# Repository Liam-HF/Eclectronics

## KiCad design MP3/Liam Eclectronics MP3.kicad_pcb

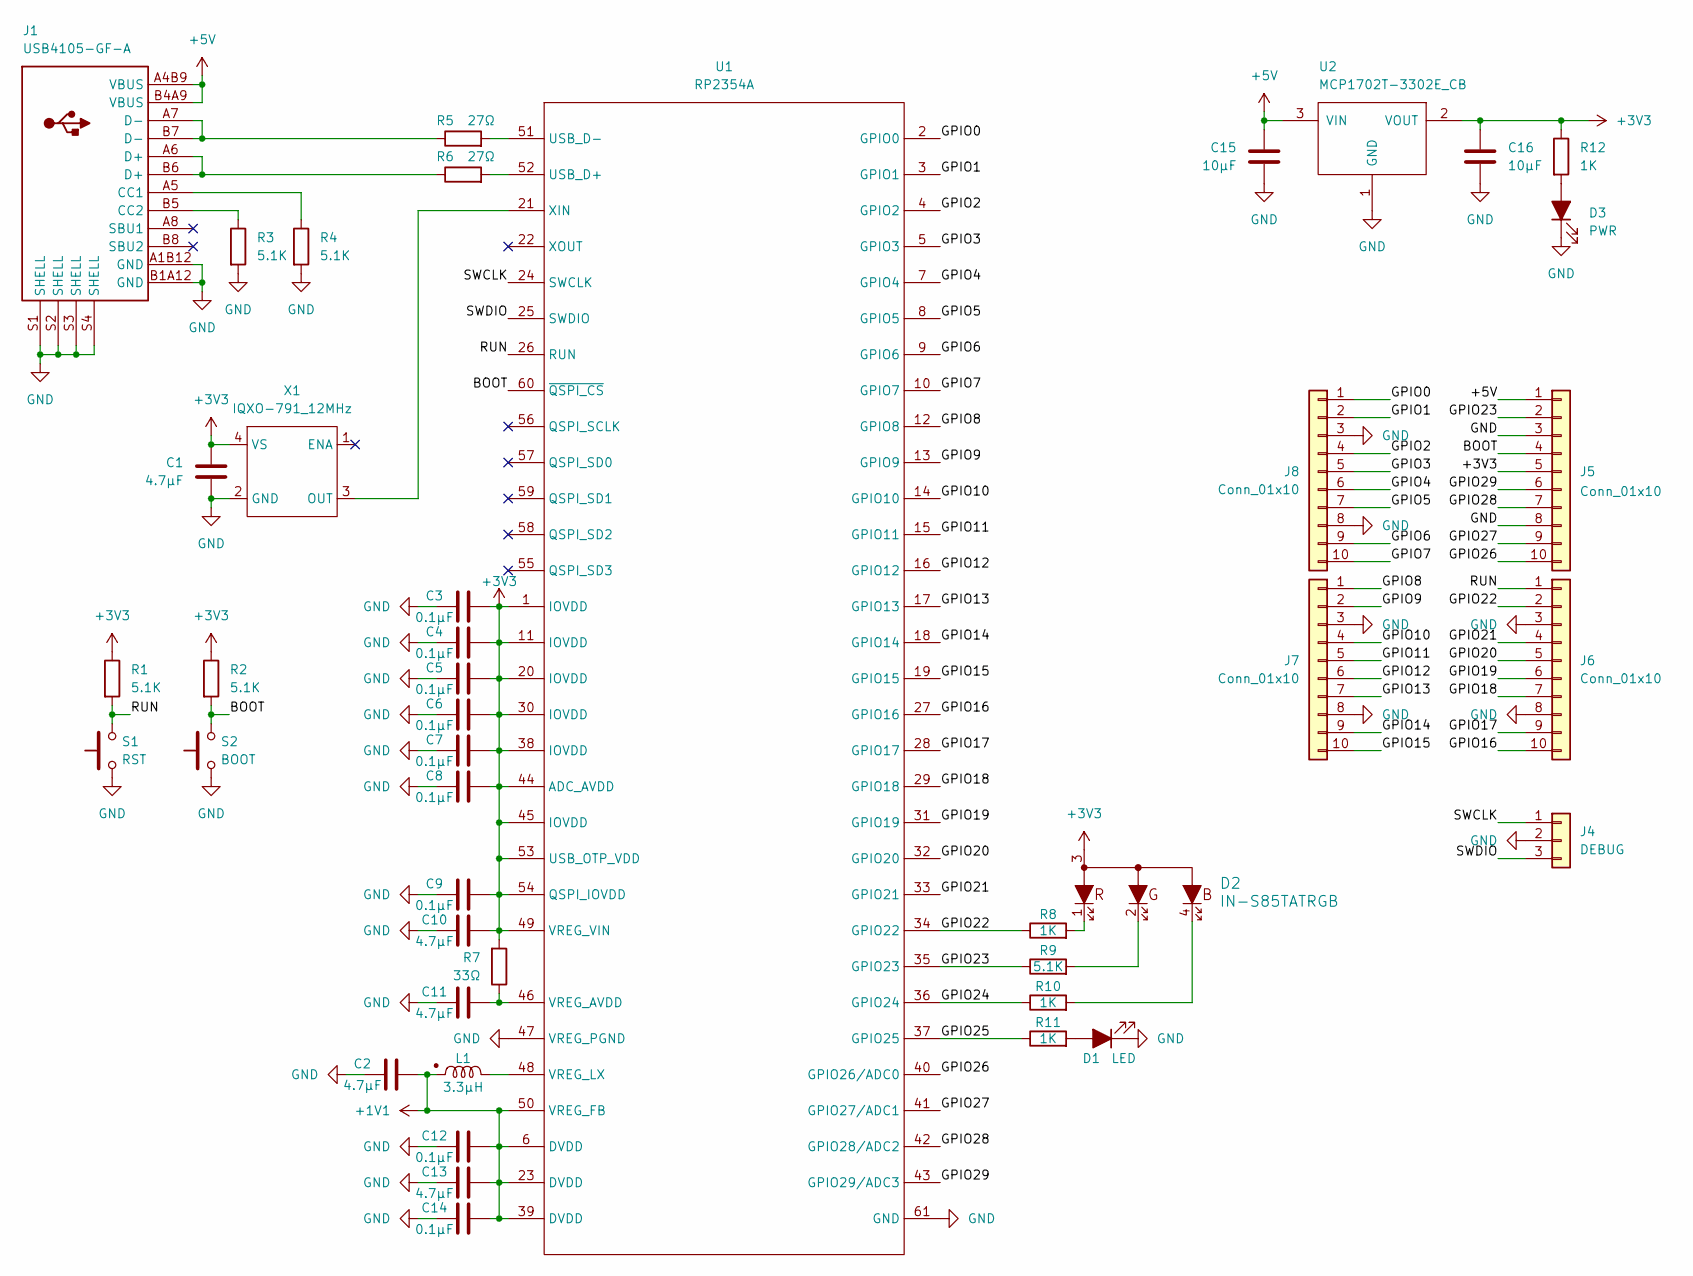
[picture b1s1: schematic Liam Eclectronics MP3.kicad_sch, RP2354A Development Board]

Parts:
C1, C2, C10, C11, C13: 4.7µF; R_0402_1005Metric
C3, C4, C5, C6, C7, C8, C9, C12, C14: 0.1µF; R_0402_1005Metric
C15, C16: 10µF; C_0603_1608Metric
D1: LED; LED_0805_2012Metric
D2: IN-S85TATRGB
D3: PWR; LED_0805_2012Metric
J1: USB4105-GF-A
J4: DEBUG; PinHeader_1x03_P2.54mm_Vertical
J5, J6, J7, J8: Conn_01x10; PinHeader_1x10_P2.54mm_Vertical
L1: 3.3µH; AOTA-B201610S3R3-101-T
R1, R2, R3, R4, R9: 5.1K; R_0402_1005Metric
R5, R6: 27Ω; R_0402_1005Metric
R7: 33Ω; R_0402_1005Metric
R8, R10, R11, R12: 1K; R_0402_1005Metric
S1: RST; B3U-1000P
S2: BOOT; B3U-1000P
U1: RP2354A; RP2350A_QFN-60_EP_7.75x7.75_Pitch0.4mm
U2: MCP1702T-3302E_CB; SOT-23
X1: IQXO-791_12MHz; IQXO-791

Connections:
+1V1: C2.2, C12.2, C13.2, C14.2, L1.1, U1.6 (DVDD), U1.23 (DVDD), U1.39 (DVDD), U1.50 (VREG_FB)
+3V3: C1.2, C3.2, C4.2, C5.2, C6.2, C7.2, C8.2, C9.2, C10.2, C16.1, D2.3, J5.5, R1.1, R2.1, R7.2, R12.1, U1.1 (IOVDD), U1.11 (IOVDD), U1.20 (IOVDD), U1.30 (IOVDD), U1.38 (IOVDD), U1.44 (ADC_AVDD), U1.45 (IOVDD), U1.49 (VREG_VIN), U1.53 (USB_OTP_VDD), U1.54 (QSPI_IOVDD), U2.2 (VOUT), X1.4 (VS)
+5V: C15.2, J1.A4B9 (VBUS), J1.B4A9 (VBUS), J5.1, U2.3 (VIN)
/BOOT: J5.4, R2.2, S2.2, U1.60 (~QSPI_CS)
/GPIO0: J8.1, U1.2 (GPIO0)
/GPIO1: J8.2, U1.3 (GPIO1)
/GPIO2: J8.4, U1.4 (GPIO2)
/GPIO3: J8.5, U1.5 (GPIO3)
/GPIO4: J8.6, U1.7 (GPIO4)
/GPIO5: J8.7, U1.8 (GPIO5)
/GPIO6: J8.9, U1.9 (GPIO6)
/GPIO7: J8.10, U1.10 (GPIO7)
/GPIO8: J7.1, U1.12 (GPIO8)
/GPIO9: J7.2, U1.13 (GPIO9)
/GPIO10: J7.4, U1.14 (GPIO10)
/GPIO11: J7.5, U1.15 (GPIO11)
/GPIO12: J7.6, U1.16 (GPIO12)
/GPIO13: J7.7, U1.17 (GPIO13)
/GPIO14: J7.9, U1.18 (GPIO14)
/GPIO15: J7.10, U1.19 (GPIO15)
/GPIO16: J6.10, U1.27 (GPIO16)
/GPIO17: J6.9, U1.28 (GPIO17)
/GPIO18: J6.7, U1.29 (GPIO18)
/GPIO19: J6.6, U1.31 (GPIO19)
/GPIO20: J6.5, U1.32 (GPIO20)
/GPIO21: J6.4, U1.33 (GPIO21)
/GPIO22: J6.2, R8.1, U1.34 (GPIO22)
/GPIO23: J5.2, R9.1, U1.35 (GPIO23)
/GPIO24: R10.1, U1.36 (GPIO24)
/GPIO25: R11.1, U1.37 (GPIO25)
/GPIO26: J5.10, U1.40 (GPIO26/ADC0)
/GPIO27: J5.9, U1.41 (GPIO27/ADC1)
/GPIO28: J5.7, U1.42 (GPIO28/ADC2)
/GPIO29: J5.6, U1.43 (GPIO29/ADC3)
/RUN: J6.1, R1.2, S1.2, U1.26 (RUN)
/SWCLK: J4.1, U1.24 (SWCLK)
/SWDIO: J4.3, U1.25 (SWDIO)
GND: C1.1, C2.1, C3.1, C4.1, C5.1, C6.1, C7.1, C8.1, C9.1, C10.1, C11.1, C12.1, C13.1, C14.1, C15.1, C16.2, D1.1 (K), D3.1 (K), J1.A1B12 (GND), J1.B1A12 (GND), J1.S1 (SHELL), J1.S2 (SHELL), J1.S3 (SHELL), J1.S4 (SHELL), J4.2, J5.3, J5.8, J6.3, J6.8, J7.3, J7.8, J8.3, J8.8, R3.2, R4.2, S1.1, S2.1, U1.47 (VREG_PGND), U1.61 (GND), U2.1 (GND), X1.2 (GND)
unnamed: D1.2 (A), R11.2
unnamed: D2.1, R8.2
unnamed: D2.2, R9.2
unnamed: D2.4, R10.2
unnamed: D3.2 (A), R12.2
unnamed: J1.A5 (CC1), R4.1
unnamed: J1.B5 (CC2), R3.1
unnamed: J1.A6 (D+), J1.B6 (D+), R6.1
unnamed: J1.A7 (D-), J1.B7 (D-), R5.1
unnamed: R6.2, U1.52 (USB_D+)
unnamed: R5.2, U1.51 (USB_D-)
unnamed: C11.2, R7.1, U1.46 (VREG_AVDD)
unnamed: L1.2, U1.48 (VREG_LX)
unnamed: U1.21 (XIN), X1.3 (OUT)

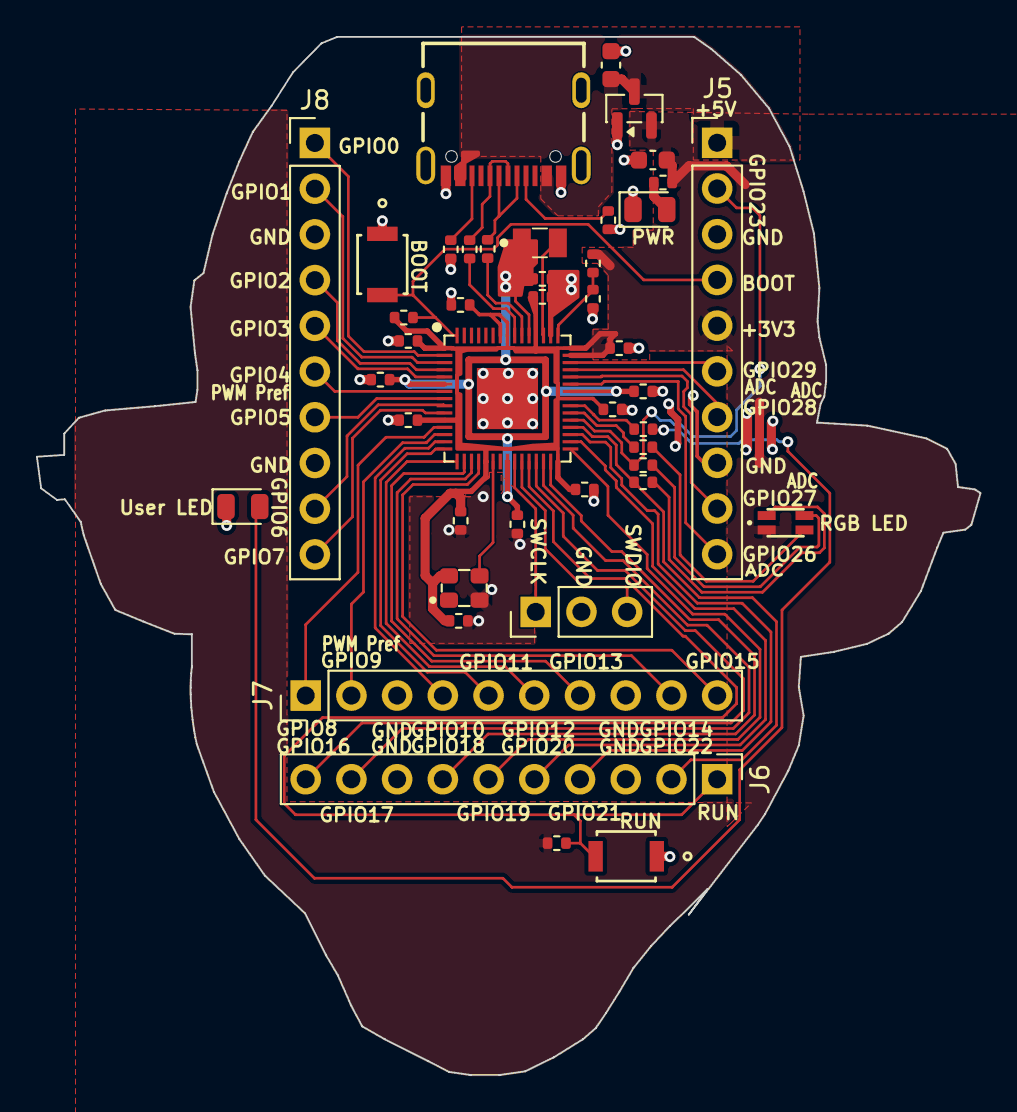
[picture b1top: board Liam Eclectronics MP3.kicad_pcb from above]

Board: 2 copper layers, 52.4 x 57.7 mm, 43 parts (0 on the bottom side), 52 nets.

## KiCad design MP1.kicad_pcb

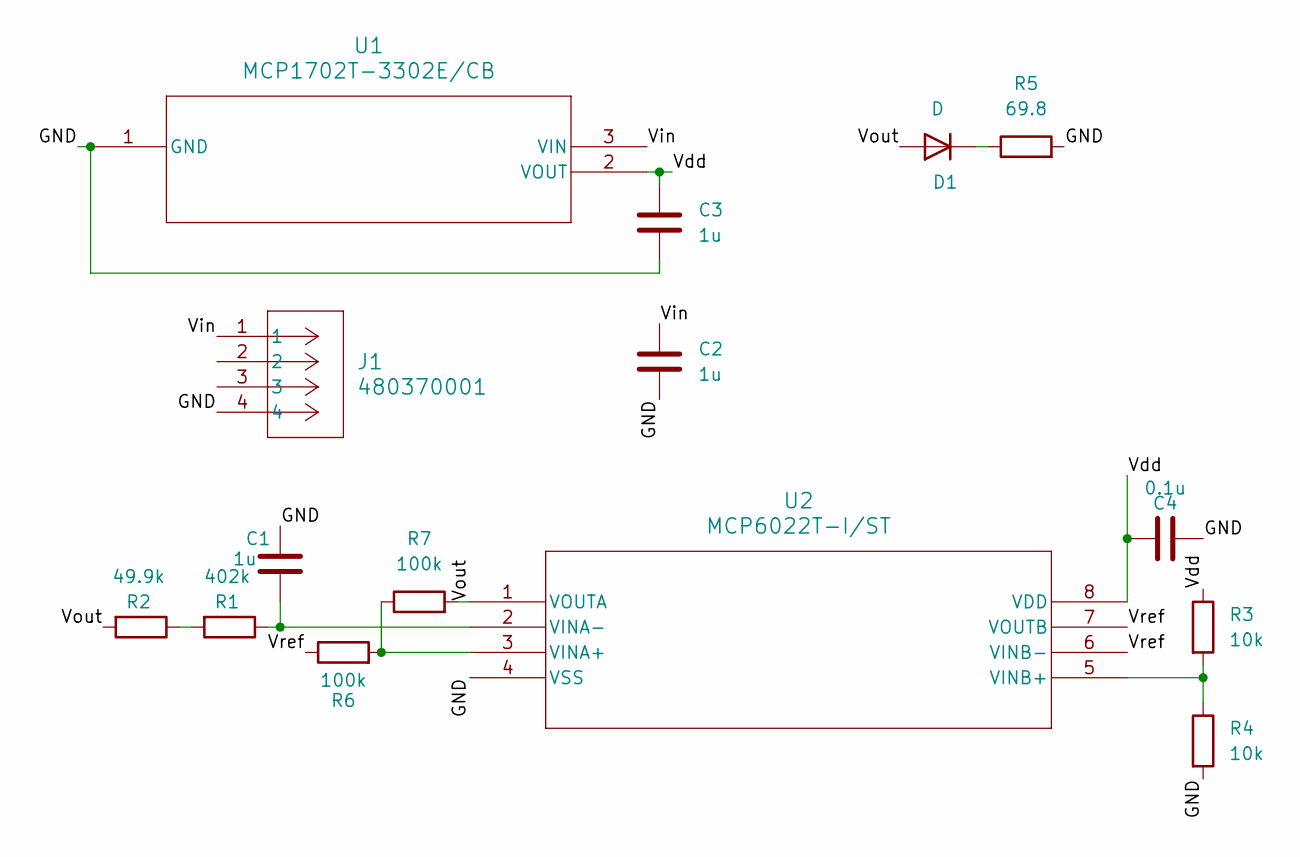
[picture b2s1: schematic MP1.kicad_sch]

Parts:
C1, C2, C3: 1u; C_0603_1608Metric
C4: 0.1u; C_0603_1608Metric
D1: D; D_0805_2012Metric
J1: 480370001; CONN_480370001_MOL
R1: 402k; R_0603_1608Metric
R2: 49.9k; R_0603_1608Metric
R3, R4: 10k; R_0603_1608Metric
R5: 69.8; R_0603_1608Metric
R6, R7: 100k; R_0603_1608Metric
U1: MCP1702T-3302E/CB; SOT-23A_MC_MCH
U2: MCP6022T-I/ST; TSSOP8_MC_MCH

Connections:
/GND: C1.1, C2.2, C3.2, C4.2, J1.4, R4.2, R5.2, U1.1 (GND), U2.4 (VSS)
/Vdd: C3.1, C4.1, R3.1, U1.2 (VOUT), U2.8 (VDD)
/Vin: C2.1, J1.1, U1.3 (VIN)
/Vout: D1.2 (A), R2.2, R7.2, U2.1 (VOUTA)
/Vref: R6.1, U2.6 (VINB-), U2.7 (VOUTB)
unnamed: D1.1 (K), R5.1
unnamed: R1.2, R2.1
unnamed: R6.2, R7.1, U2.3 (VINA+)
unnamed: C1.2, R1.1, U2.2 (VINA-)
unnamed: R3.2, R4.1, U2.5 (VINB+)

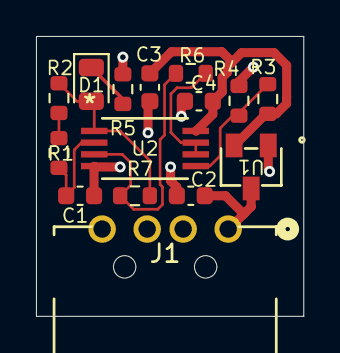
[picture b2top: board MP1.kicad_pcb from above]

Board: 2 copper layers, 14.8 x 15.5 mm, 15 parts (0 on the bottom side), 10 nets.
